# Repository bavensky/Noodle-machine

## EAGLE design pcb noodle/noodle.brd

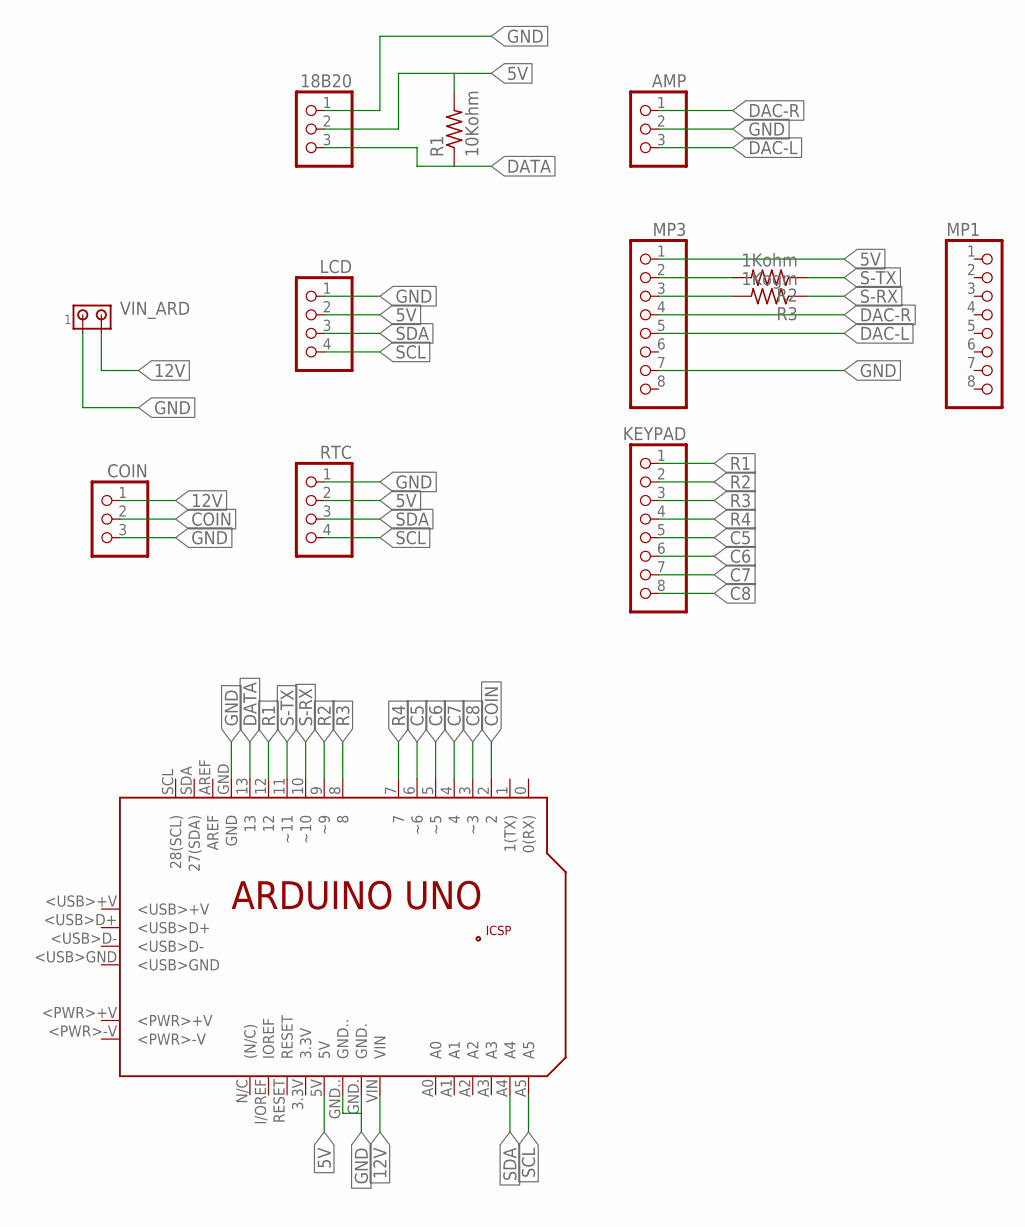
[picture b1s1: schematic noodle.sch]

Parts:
18B20: PINHD-1X3; 1X03
AMP: PINHD-1X3; 1X03
COIN: PINHD-1X3; 1X03
KEYPAD: PINHD-1X8; 1X08
LCD: PINHD-1X4; 1X04
MP1, MP3: PINHD-1X8; 1X08
PCB1: ARDUINO_UNO
R1: 10Kohm; 0207/10
R2: 1Kohm; 0207/10
R3: 1Kogm; 0207/10
RTC: PINHD-1X4; 1X04
VIN_ARD: MTA02-156; 1X2MTA

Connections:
5V: 18B20.2, LCD.2, MP3.1, PCB1.5V, R1.2, RTC.2
12V: COIN.1, PCB1.VIN, VIN_ARD.2
C5: KEYPAD.5, PCB1.6 (~6)
C6: KEYPAD.6, PCB1.5 (~5)
C7: KEYPAD.7, PCB1.4
C8: KEYPAD.8, PCB1.3 (~3)
COIN: COIN.2, PCB1.2
DAC-L: AMP.3, MP3.5
DAC-R: AMP.1, MP3.4
DATA: 18B20.3, PCB1.13, R1.1
GND: 18B20.1, AMP.2, COIN.3, LCD.1, MP3.7, PCB1.GND, PCB1.GND., PCB1.GND.., RTC.1, VIN_ARD.1
unnamed: MP3.2, R2.2
unnamed: MP3.3, R3.2
R1: KEYPAD.1, PCB1.12
R2: KEYPAD.2, PCB1.9 (~9)
R3: KEYPAD.3, PCB1.8
R4: KEYPAD.4, PCB1.7
S-RX: PCB1.10 (~10), R3.1
S-TX: PCB1.11 (~11), R2.1
SCL: LCD.4, PCB1.A5, RTC.4
SDA: LCD.3, PCB1.A4, RTC.3

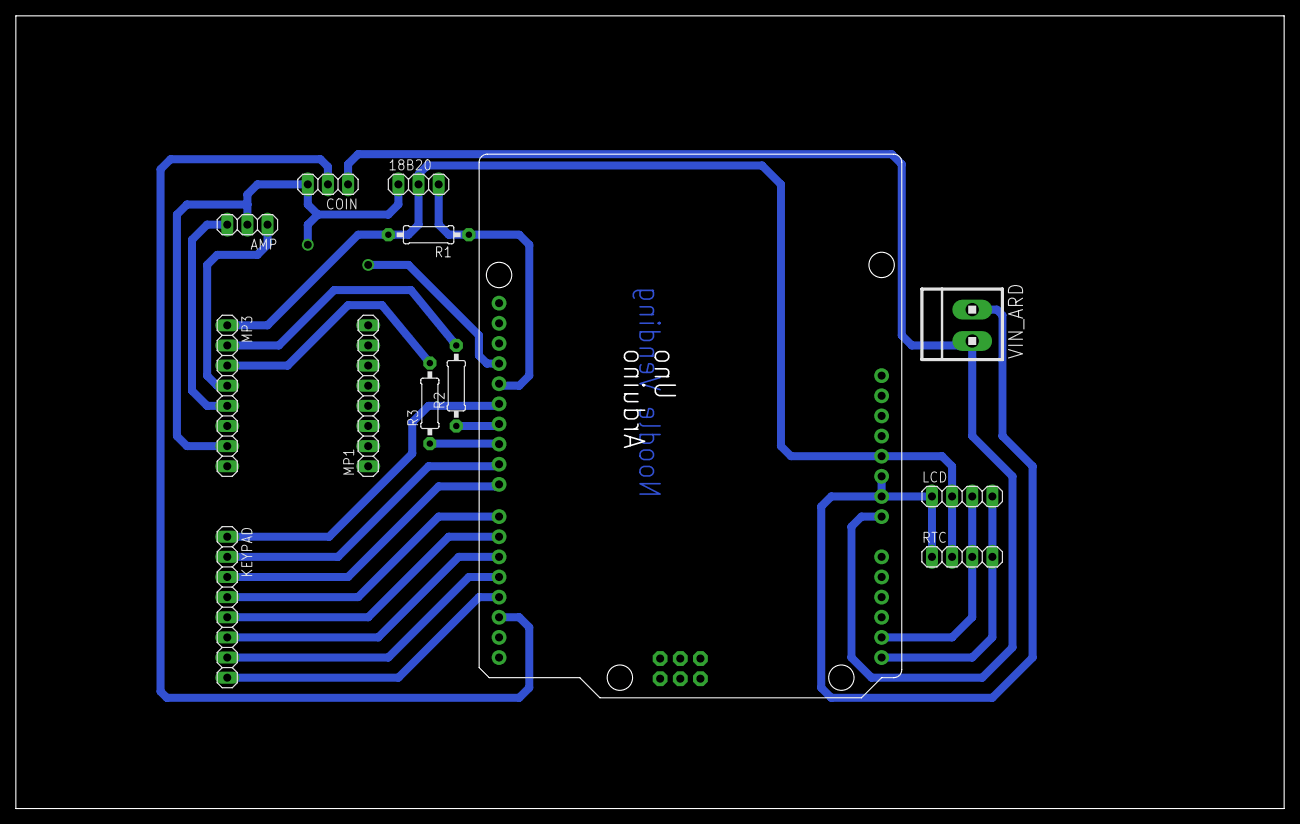
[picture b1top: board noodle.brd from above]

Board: 2 copper layers, 160.0 x 100.0 mm, 13 parts (1 on the bottom side), 21 nets.

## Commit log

2016-11-07 test 2 arduino comminication
2017-02-07 main mcu
2017-04-07 add 4 mode; 1) select noodle 2)admin mode 3)System monitor 4)get noodle
2017-04-07 no message
2017-04-08 add sound
2017-04-08 add pin control
2017-05-04 update : turn on the light when ths darkness come add mode sound 4 and 5 for pickup noodle and hot water is already add water flow sensor state
2017-06-05 update : ca money input
2017-07-05 debug machine :
    add check noodle stock
2017-07-11 update comment code
2017-07-11 add comment
2017-07-13 update code
2017-07-14 comment code
2017-07-17 update comment
2017-07-19 update code slave
2017-08-20 finaly code
2018-01-28 update new code for new pcb file
2018-03-06 add pcb file
2018-04-12 add warning chang coin
2018-04-12 add coin checked
2018-04-18 update check clear water filter
